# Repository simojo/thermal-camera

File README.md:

# Thermal camera based on Raspberry Pi Pico and MLX90640

## Overview

This camera was a dream I've had for a while to use up some parts I had lying
around on my bench. I took an embedded system design course in Fall 2025 under
Linden McClure, and I used it as an opportunity to prototype a design using wire
wrapping. The code worked, and I could use it as a thermal camera, but in April
2026, I finally taped it out to a PCB which is conducive to an enclosure and
being more rugged. I wrote the library for displaying to the thin-film
transistor display manually as the key effort to the project.

## User features

* 7 FPS refresh rate
* Dynamic color mapping
* Real-time temperature readout (min/max)
* USB-C charging
* 3.7V Lithium polymer/ion battery

## Technical Features

* CMake based project
* KiCad based layout
* Supports charging over battery
* MCP73831 charger with charging/full indicators
* 3.3V logic and power

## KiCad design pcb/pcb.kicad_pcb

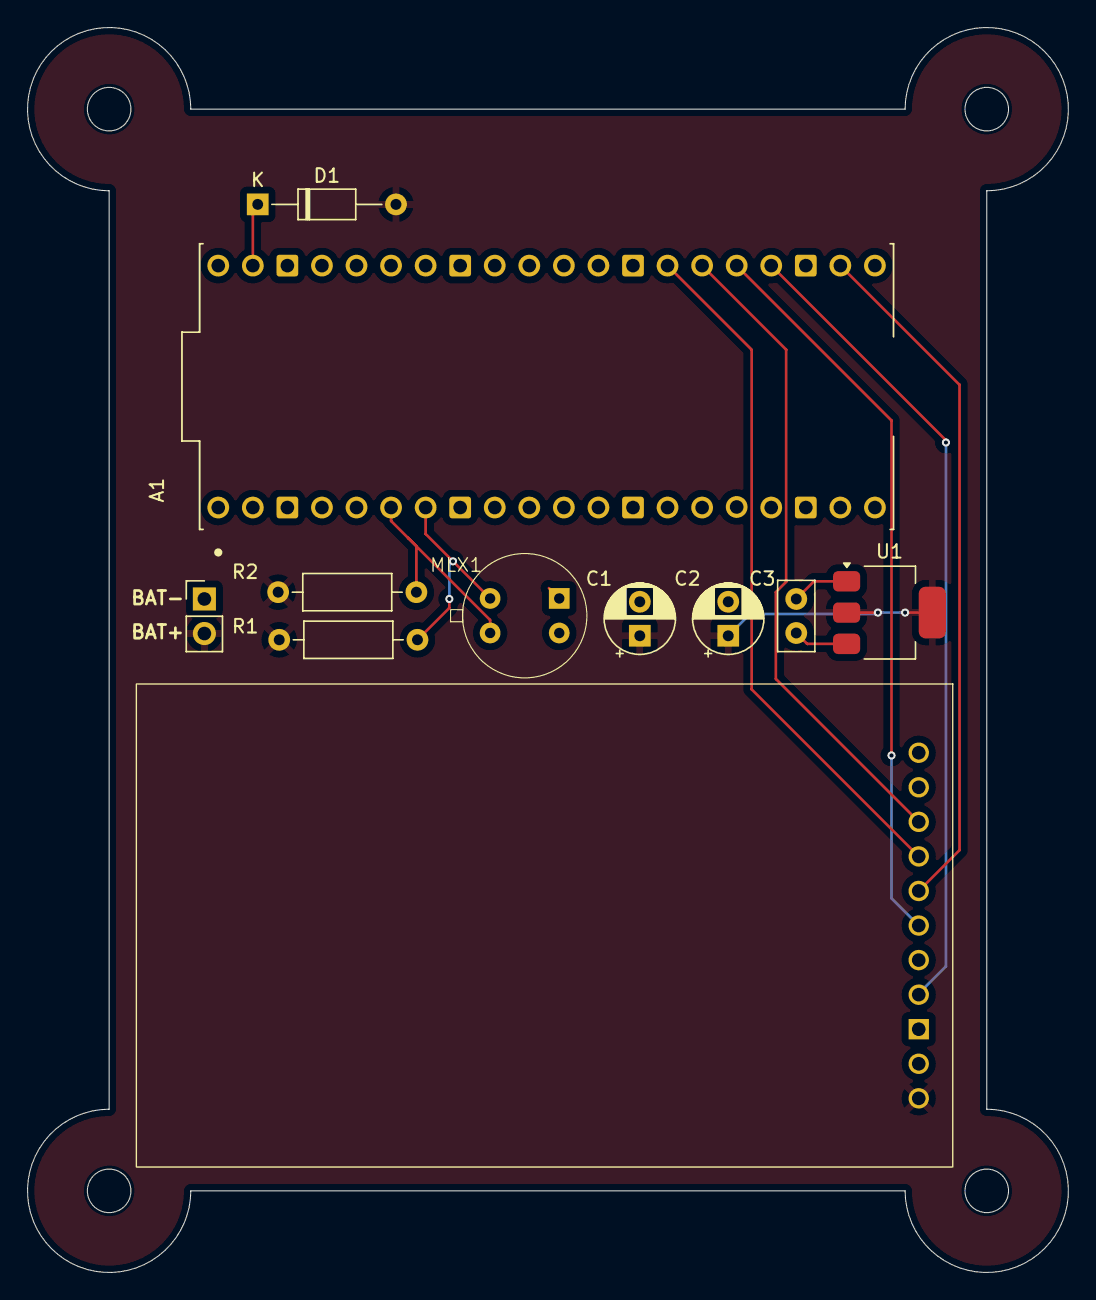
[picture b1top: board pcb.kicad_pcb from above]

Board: 2 copper layers, 76.5 x 91.5 mm, 10 parts (0 on the bottom side), 11 nets.

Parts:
A1: SC0918; RPi_Pico_SC0918
C1, C2: 1u; CP_Radial_D5.0mm_P2.50mm
C3: 0.1u; C_Disc_D5.0mm_W2.5mm_P2.50mm
D1: D_Schottky; D_DO-35_SOD27_P10.16mm_Horizontal
MLX1: MLX90640
R1, R2: 2k; R_Axial_DIN0207_L6.3mm_D2.5mm_P10.16mm_Horizontal
SST1: Adafruit-ST7789
U1: LD1117S33TR_SOT223; SOT-223-3_TabPin2

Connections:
GND: A1.38 (GND), C1.2, C2.2, C3.2, MLX1.4 (GND), SST1.9 (GND), U1.1 (GND)
unnamed: A1.6 (GP4), MLX1.1 (SDA), R2.2
unnamed: A1.7 (GP5), MLX1.2 (SCL), R1.2
unnamed: A1.22 (GP17), SST1.5 (~CS)
unnamed: A1.24 (GP18), SST1.8 (SCK)
unnamed: A1.25 (GP19), SST1.6 (MOSI)
unnamed: A1.26 (GP20), SST1.3 (D/C)
unnamed: A1.27 (GP21), SST1.4 (RST)
unnamed: A1.39 (VSYS), D1.1 (K)
unnamed: C3.1, U1.3 (VI)
VDD: C1.1, C2.1, D1.2 (A), R1.1, R2.1, SST1.11 (VIN), U1.2 (VO)

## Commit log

2025-10-16 feat: pico-sdk
2025-10-16 Basically init the entire project with semi-working thermal camera code.
2025-10-16 chore: gitignore
2025-11-24 chore: debugging, this is trash code potentially
2025-11-25 feat: change version of pico-sdk
2025-11-25 feat: putting pico sdk to new version
2025-11-26 feat: adding bit banged i2c; mlx90640 still fails
2025-11-26 feat: changing to pico (not w) fixes voltage level problems, but then I changed how we pushed out data over i2c_read, and things broke again. Things worked exactly once then broke.... word vomit yes,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
2025-11-27 feat: spi screen works with american flag configuration in correct orientation.
2025-11-27 chore: remove wave form dump
2025-11-28 feat: (untested) add functions for buffering mlx data, line drawing, writing words to spi
2025-11-28 feat: (untested) initializing SDA, SCL explicitly with SIO and not initing them twice
2025-11-29 feat: adding kicad schem, i2c works. No code change, but verifying that i2c works after fixing faulty mlx90640 circuitry (thanks adafruit...)
2025-11-29 fix: i2c implementation working with in-house i2c. going to rely on that moving forward. pixels are still outliers, but its okay
2025-11-30 feat: i2c works, reading temperatures works but flaots are invalid. Only one chess pattern shows too.
2025-11-30 feat: working frame buffering
2025-11-30 feat: working mutex with multicore
2025-11-30 feat: nice heatmap
2025-11-30 feat: font rendering
2025-11-30 feat: talking to hanoosh lol
2025-12-01 feat: (untested) no more frame area diffing, allowing rotations of mlx90640, drawing circles, removing scanner.h, externing thefont
2025-12-01 fix: static clip_pixel_vals and adding fonts.c to cmakelists
2025-12-01 doc: tweaking comments and error message
2025-12-03 feat: flawless loading screen, flawless temperature calc, flawless fps
2025-12-03 feat: (not working) unable to add a silly wifi feature. will revert
2025-12-03 Revert "feat: (not working) unable to add a silly wifi feature. will revert"
    This reverts commit c03468f307befe720b908f2ef61763585e224b50.
2025-12-03 feat: adding average calculation with color coding and changing target
2025-12-05 feat: kicad files
2026-01-15 feat: dt rather than fps
2026-04-27 feat: gitignore
2026-04-27 feat: pcb for first tape out
2026-04-27 feat: switch screen orientation markers to account for camera loc on pcb
2026-04-27 chore: changes to schematic
2026-04-27 feat: doc
